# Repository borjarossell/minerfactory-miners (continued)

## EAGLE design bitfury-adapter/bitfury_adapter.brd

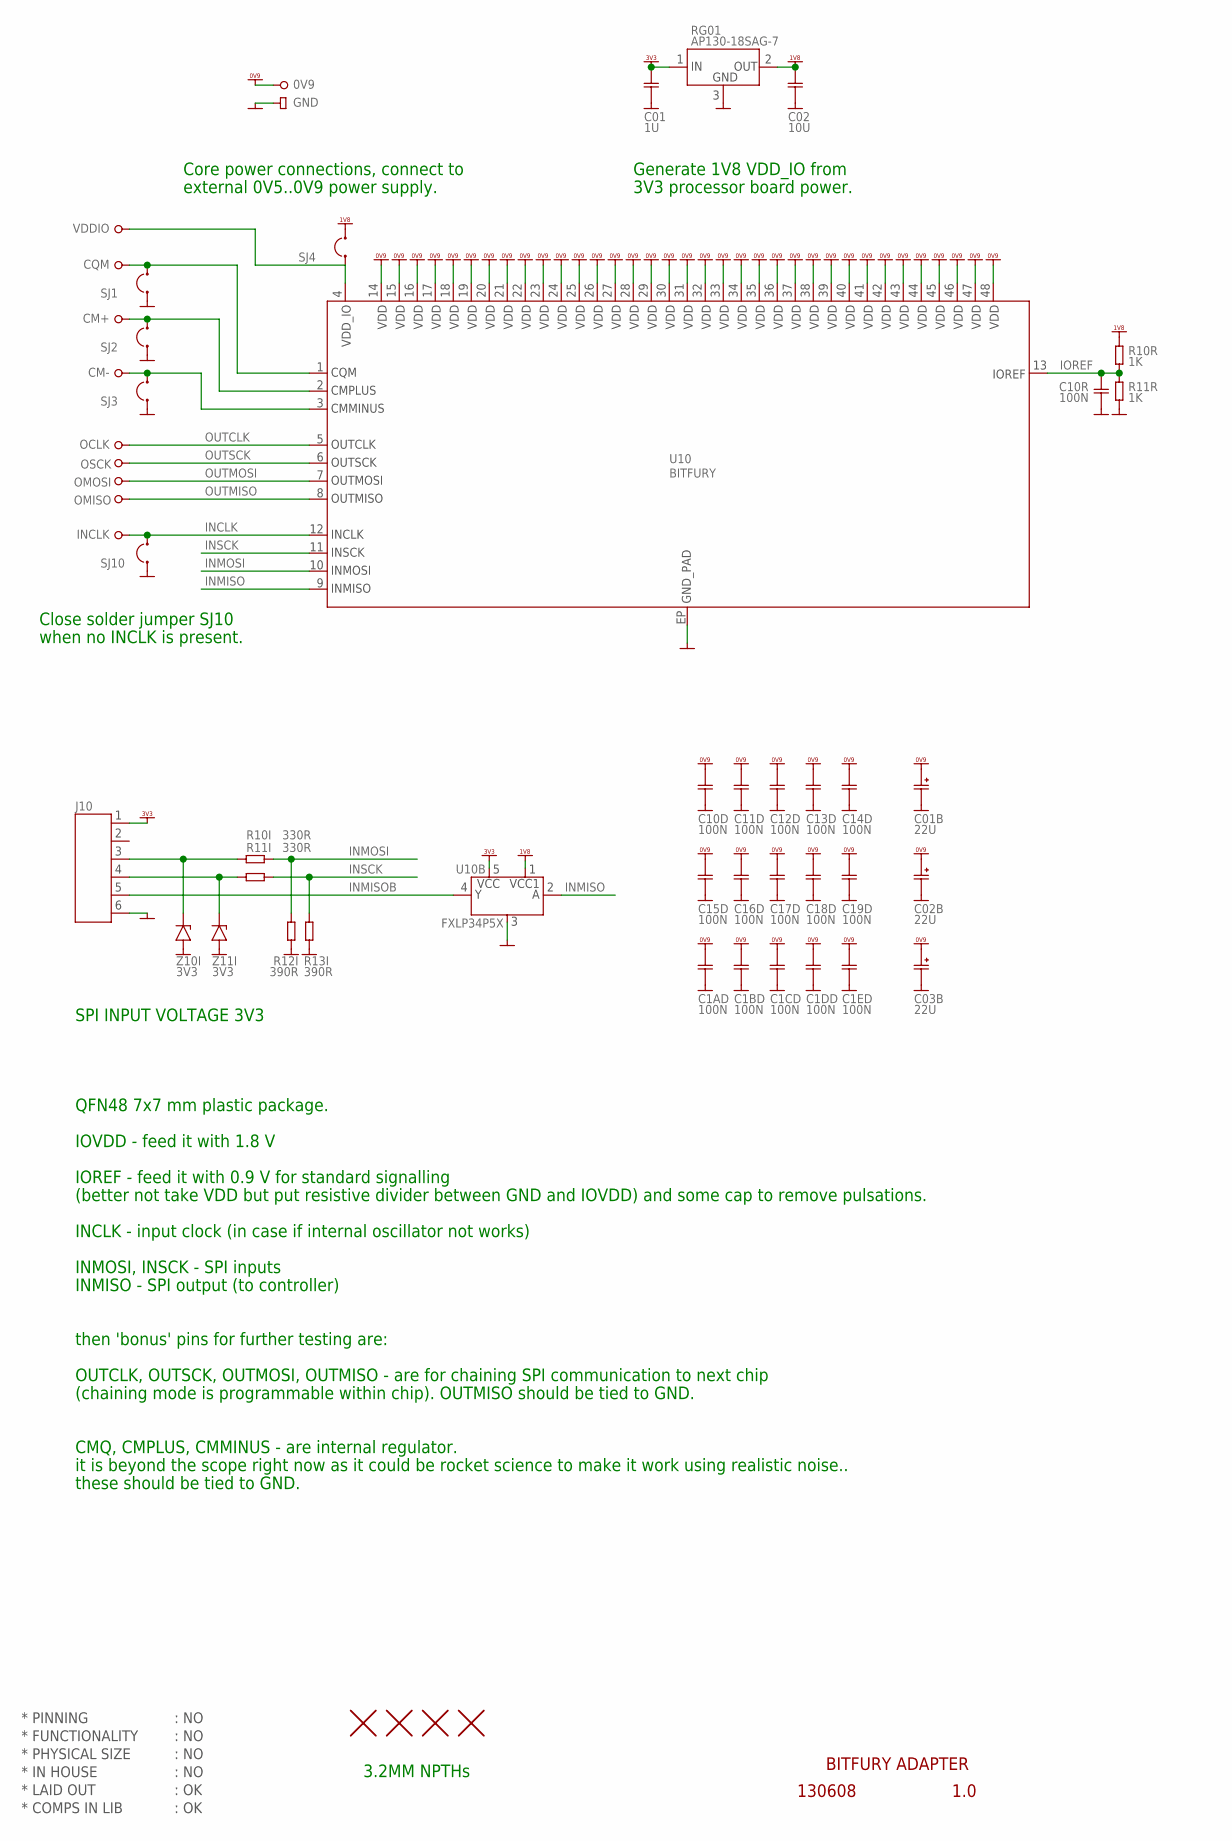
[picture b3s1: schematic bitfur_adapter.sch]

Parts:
0V9: PIN_TEST_BIG; PAD_HOLE_BIG
C01: 1U; CAP0603
C1AD, C1BD, C1CD, C1DD, C1ED, C10D, C10R, C11D, C12D, C13D, C14D, C15D, C16D, C17D, C18D, C19D: 100N; CAP0402
C01B, C02B, C03B: 22U; ECAP_SMA
C02: 10U; CAP0603
CM+: PIN_TEST; PAD_HOLE_0.8MM
CM-: PIN_TEST; PAD_HOLE_0.8MM
CQM: PIN_TEST; PAD_HOLE_0.8MM
H1, H2, H3, H4: HOLE_NPTH_3.2MM
INCLK: PIN_TEST; PAD_HOLE_0.8MM
J10: CON_MICROMATCH_6F-TOP; CON_MICROMATCH_TOP_6F
OCLK: PIN_TEST; PAD_HOLE_0.8MM
OMISO: PIN_TEST; PAD_HOLE_0.8MM
OMOSI: PIN_TEST; PAD_HOLE_0.8MM
OSCK: PIN_TEST; PAD_HOLE_0.8MM
R10I, R11I: 330R; RES0603
R10R, R11R: 1K; RES0402
R12I, R13I: 390R; RES0603
RG01: AP130-18SAG-7; SOT23
SJ1, SJ2, SJ3, SJ4, SJ10: SJ2SJ2-S; SJ2-S
U10: BITFURY; QNF48
U10B: FXLP34P5X; SOT23-5
U$83: PIN_GND; PAD_HOLE_SQR_1.8MM
VDDIO: PIN_TEST; PAD_HOLE_0.8MM
Z10I, Z11I: 3V3; ZENER_SOD123

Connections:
GND: C01.2, C1AD.2, C01B.-, C1BD.2, C1CD.2, C1DD.2, C1ED.2, C02.2, C02B.-, C03B.-, C10D.2, C10R.2, C11D.2, C12D.2, C13D.2, C14D.2, C15D.2, C16D.2, C17D.2, C18D.2, C19D.2, J10.6, R11R.2, R12I.1, R13I.1, RG01.3 (3.GND), SJ1.1, SJ2.1, SJ3.1, SJ10.1, U10.EP (EP.VSS_EP), U10.V1 (EP.VSS_EP), U10.V2 (EP.VSS_EP), U10.V3 (EP.VSS_EP), U10.V4 (EP.VSS_EP), U10.V5 (EP.VSS_EP), U10.V6 (EP.VSS_EP), U10.V7 (EP.VSS_EP), U10.V8 (EP.VSS_EP), U10.V9 (EP.VSS_EP), U10.V10 (EP.VSS_EP), U10.V11 (EP.VSS_EP), U10.V12 (EP.VSS_EP), U10.V13 (EP.VSS_EP), U10.V14 (EP.VSS_EP), U10.V15 (EP.VSS_EP), U10.V16 (EP.VSS_EP), U10.V17 (EP.VSS_EP), U10.V18 (EP.VSS_EP), U10.V19 (EP.VSS_EP), U10.V20 (EP.VSS_EP), U10.V21 (EP.VSS_EP), U10.V22 (EP.VSS_EP), U10.V23 (EP.VSS_EP), U10.V24 (EP.VSS_EP), U10.V25 (EP.VSS_EP), U10B.3 (3.GND), U$83.1, Z10I.1 (+), Z11I.1 (+)
INCLK: INCLK.1, SJ10.2, U10.12 (12.INCLK)
INMISO: U10.9 (9.INMISO), U10B.2 (2.A)
INMISOB: J10.5, U10B.4 (4.Y)
INMOSI: R10I.2, R12I.2, U10.10 (10.INMOSI)
INSCK: R11I.2, R13I.2, U10.11 (11.INSCK)
IOREF: C10R.1, R10R.2, R11R.1, U10.13 (13.IOREF)
unnamed: J10.3, R10I.1, Z10I.2 (-)
unnamed: J10.4, R11I.1, Z11I.2 (-)
unnamed: CM-.1, SJ3.2, U10.3 (3.CMMINUS)
unnamed: CM+.1, SJ2.2, U10.2 (2.CMPLUS)
unnamed: CQM.1, SJ1.2, U10.1 (1.QCM)
unnamed: SJ4.1, U10.4 (4.VDD_IO), VDDIO.1
OUTCLK: OCLK.1, U10.5 (5.OUTCLK)
OUTMISO: OMISO.1, U10.8 (8.OUTMISO)
OUTMOSI: OMOSI.1, U10.7 (7.OUTMOSI)
OUTSCK: OSCK.1, U10.6 (6.OUTSCK)
VDD_0V9: 0V9.1, C1AD.1, C01B.+, C1BD.1, C1CD.1, C1DD.1, C1ED.1, C02B.+, C03B.+, C10D.1, C11D.1, C12D.1, C13D.1, C14D.1, C15D.1, C16D.1, C17D.1, C18D.1, C19D.1, U10.14 (14.VDD), U10.15 (15.VDD), U10.16 (16.VDD), U10.17 (17.VDD), U10.18 (18.VDD), U10.19 (19.VDD), U10.20 (20.VDD), U10.21 (21.VDD), U10.22 (22.VDD), U10.23 (23.VDD), U10.24 (24.VDD), U10.25 (25.VDD), U10.26 (26.VDD), U10.27 (27.VDD), U10.28 (28.VDD), U10.29 (29.VDD), U10.30 (30.VDD), U10.31 (31.VDD), U10.32 (32.VDD), U10.33 (33.VDD), U10.34 (34.VDD), U10.35 (35.VDD), U10.36 (36.VDD), U10.37 (37.VDD), U10.38 (38.VDD), U10.39 (39.VDD), U10.40 (40.VDD), U10.41 (41.VDD), U10.42 (42.VDD), U10.43 (43.VDD), U10.44 (44.VDD), U10.45 (45.VDD), U10.46 (46.VDD), U10.47 (47.VDD), U10.48 (48.VDD)
VDD_1V8: C02.1, R10R.1, RG01.2 (2.OUT), SJ4.2, U10B.1 (1.VCC1)
VDD_3V3: C01.1, J10.1, RG01.1 (1.IN), U10B.5 (5.VCC)

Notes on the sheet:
* PINNING
* FUNCTIONALITY
* PHYSICAL SIZE
* LAID OUT
* COMPS IN LIB
* IN HOUSE
: NO
BITFURY ADAPTER
130608
1.0
: OK
QFN48 7x7 mm plastic package.
IOVDD - feed it with 1.8 V
IOREF - feed it with 0.9 V for standard signalling
(better not take VDD but put resistive divider between GND and IOVDD) and some cap to remove pulsations.
INCLK - input clock (in case if internal oscillator not works)
INMOSI, INSCK - SPI inputs
INMISO - SPI output (to controller)
then 'bonus' pins for further testing are:
OUTCLK, OUTSCK, OUTMOSI, OUTMISO - are for chaining SPI communication to next chip
CMQ, CMPLUS, CMMINUS - are internal regulator.
it is beyond the scope right now as it could be rocket science to make it work using realistic noise..
these should be tied to GND.
Generate 1V8 VDD_IO from
3V3 processor board power.
(chaining mode is programmable within chip). OUTMISO should be tied to GND.
3.2MM NPTHs
Close solder jumper SJ10
when no INCLK is present.
Core power connections, connect to
GND
external 0V5..0V9 power supply.
SPI INPUT VOLTAGE 3V3

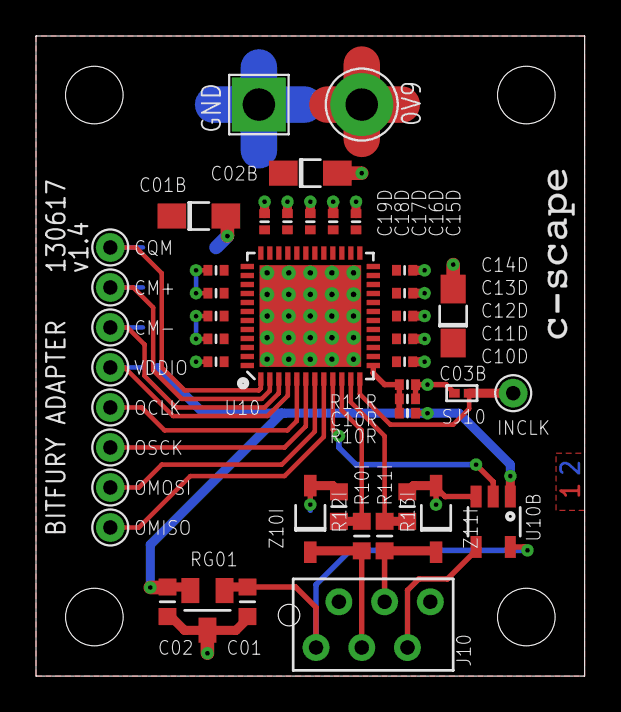
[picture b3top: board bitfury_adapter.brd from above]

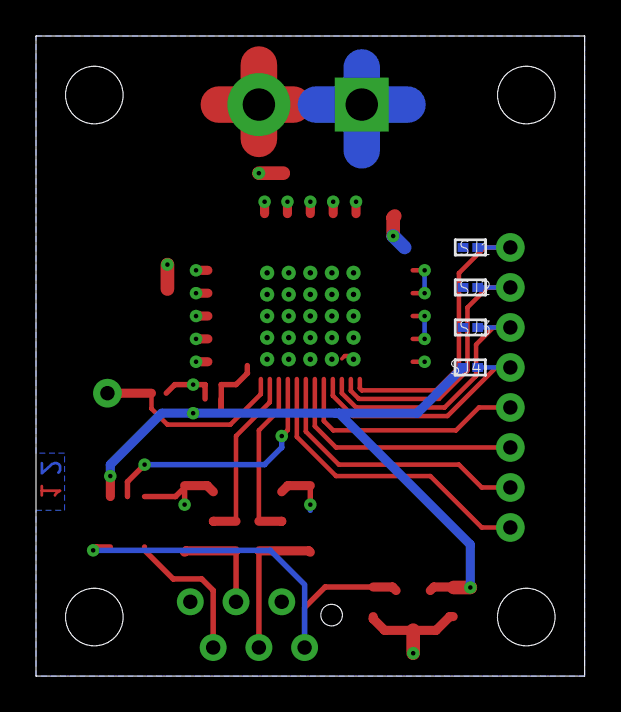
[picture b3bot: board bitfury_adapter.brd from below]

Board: 2 copper layers, 30.5 x 35.6 mm, 54 parts (4 on the bottom side), 20 nets.

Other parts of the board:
U$47: CSCAPE2

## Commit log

2015-01-01 Added litefury-4 and litefury-5 projects
2015-01-01 Added cgminer software for bitfury chips
